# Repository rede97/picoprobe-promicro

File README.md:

# picoprobe-promicro

[中文版本](README_CN.md)

---

A Raspberry Pi Debug Probe expansion board based on the **RP2040 Pro Micro** core module. The circuit is fully compatible with the [official Raspberry Pi Debug Probe](https://www.raspberrypi.com/products/debug-probe/) — simply plug a RP2040 Pro Micro onto this board, flash the **official Debug Probe firmware from Raspberry Pi**, and you're ready to go. No custom firmware needed.

The RP2040 Pro Micro has onboard **Boot** and **Reset** buttons, making firmware flashing effortless: hold Boot → press Reset → release Boot, and a USB mass storage drive appears — just drag and drop the `.uf2` firmware file. No jumper wires or complicated steps required.

## Compatibility & Reliability

What's truly surprising is how well the Raspberry Pi Debug Probe works beyond its intended target. Its compatibility and reliability are **far beyond expectations**. It not only handles RP2040 chips perfectly, but also delivers rock-solid debugging and flashing for a wide range of **ARM microcontrollers and SoCs** — the full STM32 lineup, Nordic chips like the nRF52840, and virtually any Cortex-M core MCU.

Thanks to the RP2040's **PIO hardware**, the Debug Probe achieves exceptionally fast SWD transfer speeds, matching or exceeding some USB high-speed debuggers in practice. Over long debugging sessions across various target chips, it shows none of the common issues — no disconnections, no timeouts, no failed device recognition.

## Motivation

The official Raspberry Pi Debug Probe has a few shortcomings:

- It still uses a **Micro USB** connector, while USB-C has become the standard
- Flashing Picoprobe firmware onto a bare Pico often leads to **various stability issues**
- Designing a complete dedicated debugger PCB is overkill for many users
- It's essentially just an RP2040 + level-shifting circuit — the official price is steep for a fixed-function debug board

Meanwhile, open-source DAPLink solutions generally have **worse compatibility and stability** across ARM chips compared to the Raspberry Pi Debug Probe.

## Fully Open Source

This is one of the project's biggest strengths:

- **Fully open hardware**: All PCB design files (schematic, layout) are open source in KiCad format. Anyone can inspect, modify, or order their own boards
- **Firmware is fully open source**: Uses the official Raspberry Pi [debugprobe firmware](https://github.com/raspberrypi/debugprobe) directly — no proprietary or custom code. Maintained by Raspberry Pi, continuously updated, with guaranteed quality
- **No closed-source burden**: Many DAPLink debuggers on the market ship with proprietary firmware. When bugs appear, there's no one to report to and no way to upgrade or fix yourself. This solution is open source from hardware to firmware — community-driven and never obsolete

## Regarding JTAG

This project currently supports **SWD** only, not JTAG. From a practical standpoint:

- The vast majority of Cortex-M MCU debugging and flashing only requires SWD — JTAG is not necessary
- If you genuinely need JTAG along with Trace, ETM, and other advanced debugging features, a mature **J-Link** is the better choice — at that point you need a complete professional debugging toolchain, not just a protocol interface

Future firmware-level JTAG support is not out of the question (the RP2040's PIO is capable in hardware), but there are no concrete plans at this stage.

## Design Approach

Rather than designing a complete debugger from scratch, this project pairs a widely available **RP2040 Pro Micro** module with a dedicated expansion board:

- **Flexible**: Use pin headers and female header sockets to temporarily mount the Pro Micro on the board for debugging — detach and reuse it anytime
- **Permanent option**: Solder short pin headers to permanently join the Pro Micro and the board together as a dedicated, long-term debug probe
- **Ultra-low BOM cost**: Significantly cheaper than the official Debug Probe
- **Zero pressure**: No worries about damaging an expensive debugger — hack, modify, or build your own features on top

## PCB Renders

| Front | Back |
|:---:|:---:|
|  |  |

[Download schematic PDF](hardware/picoprobe_sch.pdf)

## Real-World Photos

This debugger works perfectly with both the **Raspberry Pi Pico 2** and the **nRF52840** — rock-solid in practice, with very fast download speeds.

### 1. Detachable socket assembly

The Pro Micro is mounted on the board via pin headers and female header sockets. Plug it in to debug; pull it off anytime and reuse the module in other projects.

### 2. Soldered as one piece

The Pro Micro is soldered directly onto the board as a single, integrated unit. This version is smaller in volume, and is otherwise **functionally identical** to the detachable version — same circuit, same performance.

### 3. Debugging an nRF52840

Debugging and flashing an nRF52840 target over SWD. Works flawlessly, with very fast download speeds.

## Project Structure

```
├── hardware/
│   ├── picoprobe.kicad_sch      # Schematic
│   ├── picoprobe.kicad_pcb      # PCB layout
│   ├── picoprobe.kicad_pro      # KiCad project file
│   ├── picoprobe-front.png      # Front render
│   ├── picoprobe-back.png       # Back render
│   ├── picoprobe_sch.pdf        # Schematic PDF
│   ├── picture/                 # Real-world photos
│   └── kicad_pro_micro_rp2040/  # Pro Micro RP2040 footprint library (submodule)
├── README.md
└── README_CN.md
```

## Dependencies

- [kicad_pro_micro_rp2040](https://github.com/rroels/kicad_pro_micro_rp2040) — KiCad symbol and footprint library for the Pro Micro RP2040

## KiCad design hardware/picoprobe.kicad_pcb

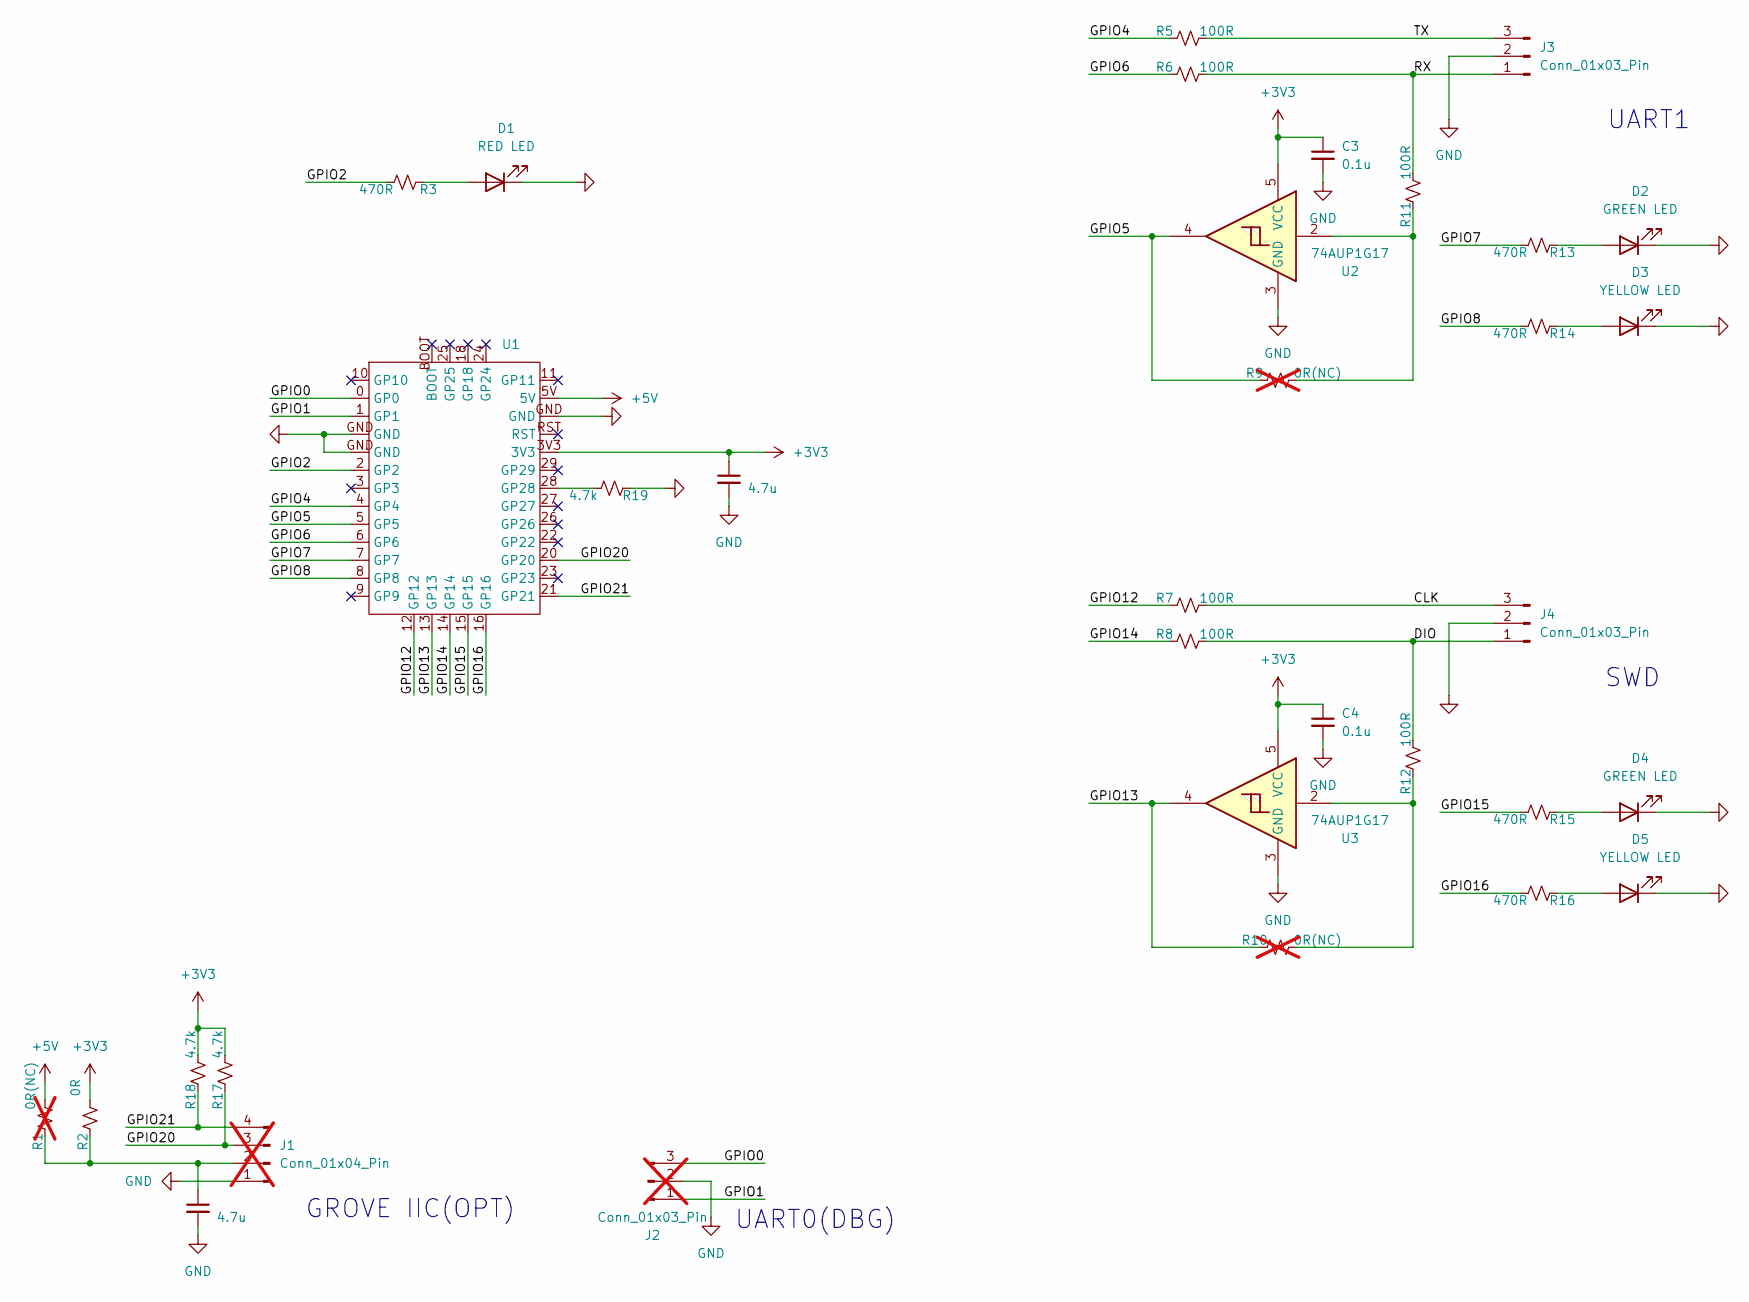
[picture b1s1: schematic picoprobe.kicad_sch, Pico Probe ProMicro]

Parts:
C1, C2: 4.7u; C_0402_1005Metric; LCSC Part C23733
C3, C4: 0.1u; C_0402_1005Metric; LCSC Part C307331
D1: RED LED; LED_0603_1608Metric; LCSC Part C2286
D2, D4: GREEN LED; LED_0603_1608Metric; LCSC Part C7496818
D3, D5: YELLOW LED; LED_0603_1608Metric; LCSC Part C965800
J1: Conn_01x04_Pin; PinHeader_1x04_P2.54mm_Vertical; not fitted
J2: Conn_01x03_Pin; PinHeader_1x03_P2.54mm_Vertical; not fitted
J3, J4: Conn_01x03_Pin; JST_XH_B3B-XH-A_1x03_P2.50mm_Vertical
R1: 0R(NC); R_0603_1608Metric; LCSC Part C21189; not fitted
R2: 0R; R_0603_1608Metric; LCSC Part C21189
R3, R13, R14, R15, R16: 470R; R_0402_1005Metric; LCSC Part C25117
R5, R6, R7, R8, R11, R12: 100R; R_0402_1005Metric; LCSC Part C25076
R9, R10: 0R(NC); R_0402_1005Metric; LCSC Part C17168; not fitted
R17, R18, R19: 4.7k; R_0402_1005Metric; LCSC Part C25900
U1: pro_micro_rp2040
U2, U3: 74AUP1G17; SOT-353_SC-70-5; LCSC Part C48946883

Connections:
+3V3: C2.1, C3.1, C4.1, R2.2, R17.2, R18.2, U1.3V3, U2.5 (VCC), U3.5 (VCC)
+5V: R1.2, U1.5V
/CLK: J4.3, R7.2
/DIO: J4.1, R8.2, R12.2
/GPIO0: J2.3, U1.0 (GP0)
/GPIO1: J2.1, U1.1 (GP1)
/GPIO2: R3.2, U1.2 (GP2)
/GPIO4: R5.1, U1.4 (GP4)
/GPIO5: R9.1, U1.5 (GP5), U2.4
/GPIO6: R6.1, U1.6 (GP6)
/GPIO7: R13.2, U1.7 (GP7)
/GPIO8: R14.2, U1.8 (GP8)
/GPIO12: R7.1, U1.12 (GP12)
/GPIO13: R10.1, U1.13 (GP13), U3.4
/GPIO14: R8.1, U1.14 (GP14)
/GPIO15: R15.2, U1.15 (GP15)
/GPIO16: R16.2, U1.16 (GP16)
/GPIO20: J1.3, R17.1, U1.20 (GP20)
/GPIO21: J1.4, R18.1, U1.21 (GP21)
/RX: J3.1, R6.2, R11.2
/TX: J3.3, R5.2
GND: C1.2, C2.2, C3.2, C4.2, D1.1 (K), D2.1 (K), D3.1 (K), D4.1 (K), D5.1 (K), J1.1, J2.2, J3.2, J4.2, R19.1, U1.GND, U2.3 (GND), U3.3 (GND)
unnamed: D1.2 (A), R3.1
unnamed: D2.2 (A), R13.1
unnamed: D3.2 (A), R14.1
unnamed: D4.2 (A), R15.1
unnamed: D5.2 (A), R16.1
unnamed: C1.1, J1.2, R1.1, R2.1
unnamed: R10.2, R12.1, U3.2
unnamed: R9.2, R11.1, U2.2
unnamed: R19.2, U1.28 (GP28)

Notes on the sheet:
UART0(DBG)
UART1
SWD
GROVE IIC(OPT)

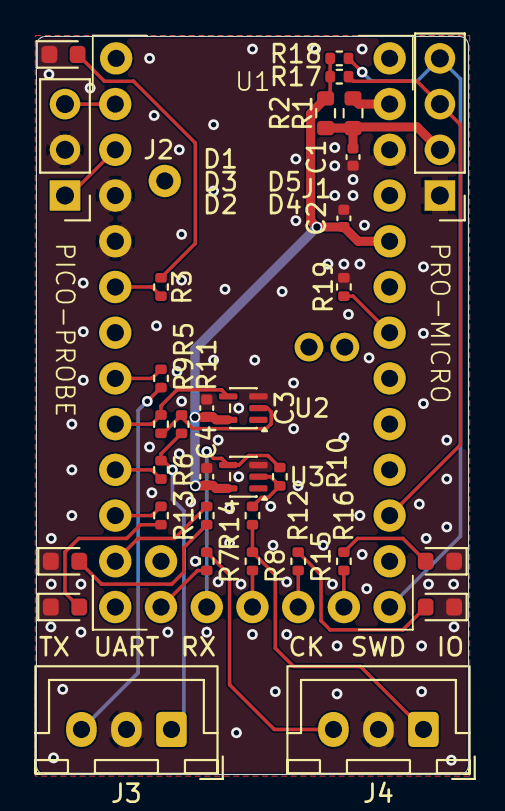
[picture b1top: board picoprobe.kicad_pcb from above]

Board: 2 copper layers, 24.0 x 41.0 mm, 34 parts (0 on the bottom side), 31 nets.

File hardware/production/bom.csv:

Designator,Footprint,Quantity,Value,LCSC Part #
"C1, C2",0402,2,4.7u,C23733
"C3, C4",0402,2,0.1u,C307331
D1,0603,1,RED LED,C2286
"D2, D4",0603,2,GREEN LED,C7496818
"D3, D5",0603,2,YELLOW LED,C965800
J1,PinHeader_1x04_P2.54mm_Vertical,1,Conn_01x04_Pin,
J2,PinHeader_1x03_P2.54mm_Vertical,1,Conn_01x03_Pin,
"J3, J4",JST_XH_B3B-XH-A_1x03_P2.50mm_Vertical,2,Conn_01x03_Pin,
"R1, R10, R9",0402,3,0R(NC),C17168
"R11, R12, R5, R6, R7, R8",0402,6,100R,C25076
"R13, R14, R15, R16, R3",0402,5,470R,C25117
"R17, R18, R19",0402,3,4.7k,C25900
R2,0402,1,0R,C17168
U1,pro_micro_rp2040,1,~,
"U2, U3",SOT-23-5,2,74AUP1G17,C48946883

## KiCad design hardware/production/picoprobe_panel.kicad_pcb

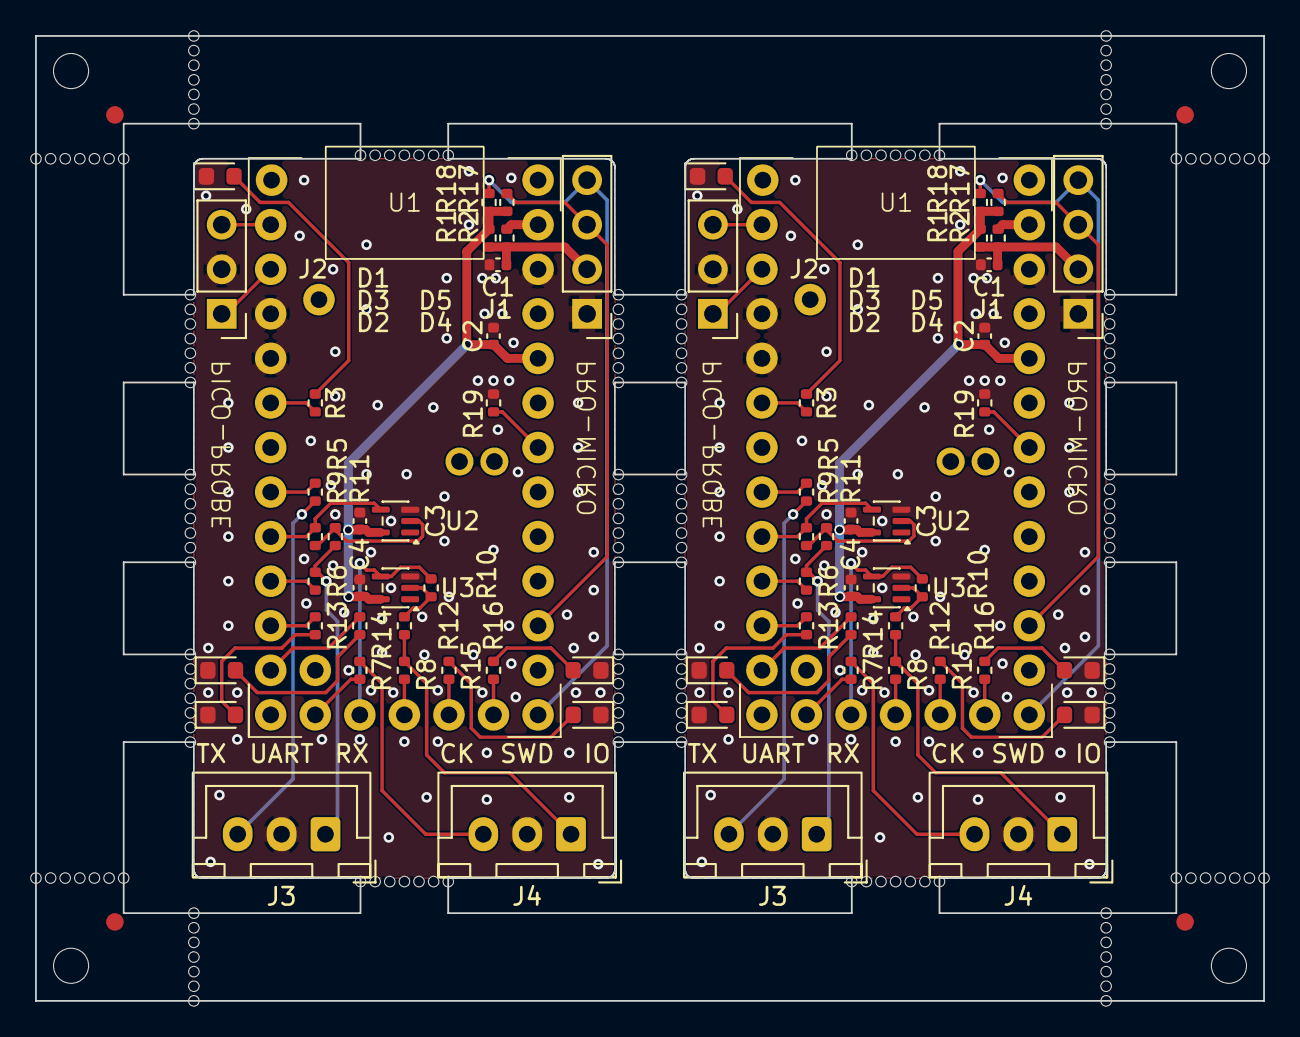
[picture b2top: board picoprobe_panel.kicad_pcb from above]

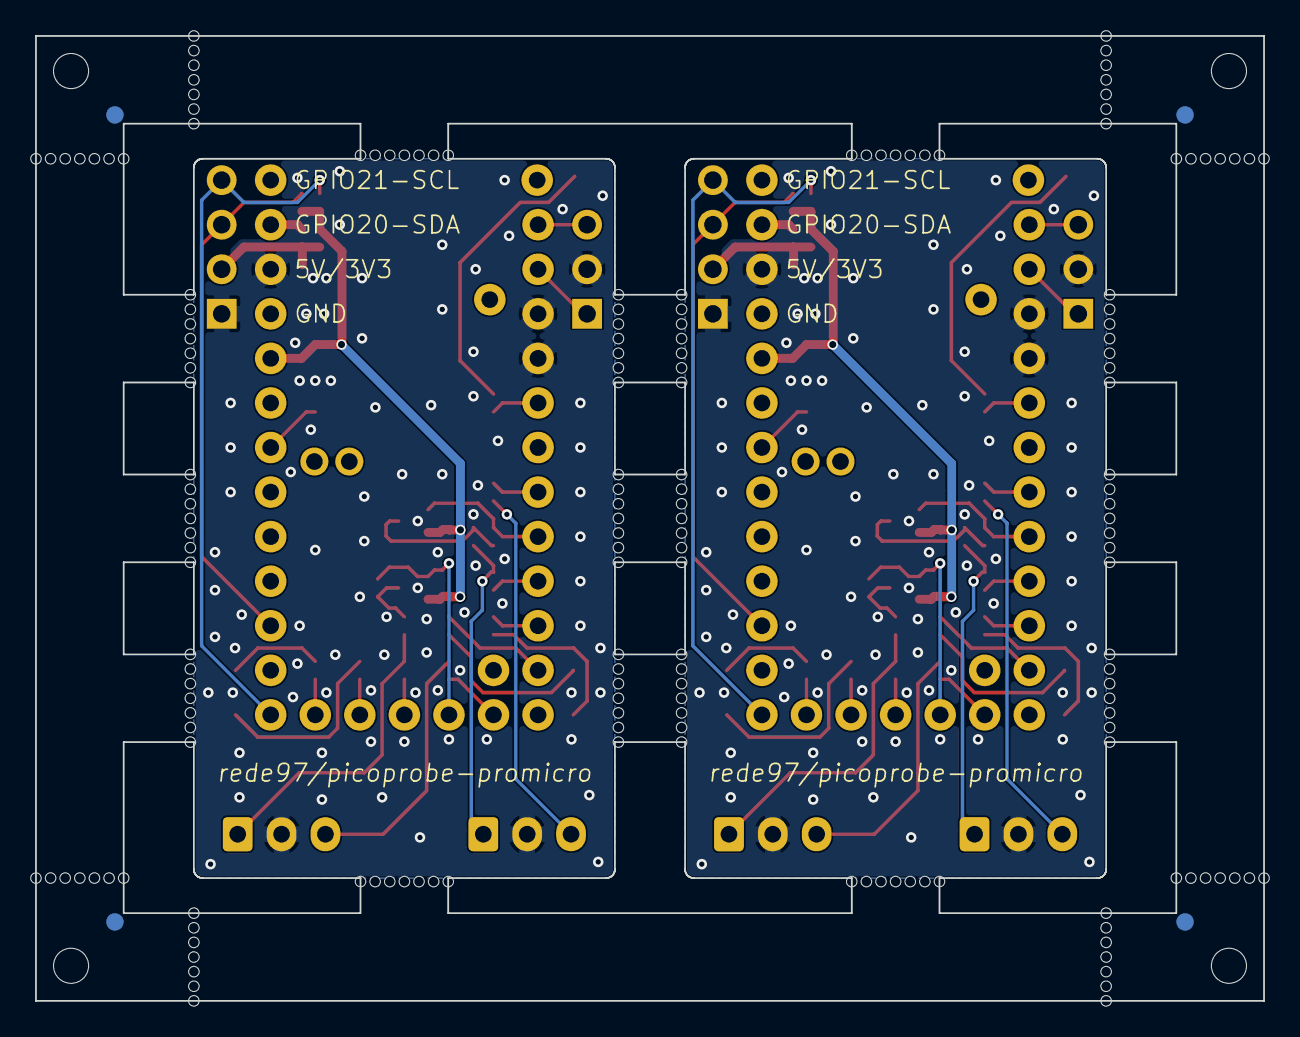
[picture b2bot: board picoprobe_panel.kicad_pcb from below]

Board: 2 copper layers, 70.0 x 55.0 mm, 248 parts (4 on the bottom side), 62 nets.

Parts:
C1, C1#2, C2, C2#2: 4.7u; C_0402_1005Metric
C3, C3#2, C4, C4#2: 0.1u; C_0402_1005Metric
D1, D1#2: RED LED; LED_0603_1608Metric
D2, D2#2, D4, D4#2: GREEN LED; LED_0603_1608Metric
D3, D3#2, D5, D5#2: YELLOW LED; LED_0603_1608Metric
J1, J1#2: Conn_01x04_Pin; PinHeader_1x04_P2.54mm_Vertical
J2, J2#2: Conn_01x03_Pin; PinHeader_1x03_P2.54mm_Vertical
J3, J3#2, J4, J4#2: Conn_01x03_Pin; JST_XH_B3B-XH-A_1x03_P2.50mm_Vertical
KiKit_FID_B_1, KiKit_FID_B_2, KiKit_FID_B_3, KiKit_FID_B_4: Fiducial
KiKit_FID_T_1, KiKit_FID_T_2, KiKit_FID_T_3, KiKit_FID_T_4: Fiducial
KiKit_MB_1_1, KiKit_MB_1_2, KiKit_MB_1_3, KiKit_MB_1_4, KiKit_MB_1_5, KiKit_MB_1_6, KiKit_MB_1_7, KiKit_MB_2_1, KiKit_MB_2_2, KiKit_MB_2_3, KiKit_MB_2_4, KiKit_MB_2_5, KiKit_MB_2_6, KiKit_MB_2_7, KiKit_MB_3_1, KiKit_MB_3_2, KiKit_MB_3_3, KiKit_MB_3_4, KiKit_MB_3_5, KiKit_MB_3_6, KiKit_MB_3_7, KiKit_MB_4_1, KiKit_MB_4_2, KiKit_MB_4_3, KiKit_MB_4_4, KiKit_MB_4_5, KiKit_MB_4_6, KiKit_MB_4_7, KiKit_MB_5_1, KiKit_MB_5_2, KiKit_MB_5_3, KiKit_MB_5_4, KiKit_MB_5_5, KiKit_MB_5_6, KiKit_MB_5_7, KiKit_MB_6_1, KiKit_MB_6_2, KiKit_MB_6_3, KiKit_MB_6_4, KiKit_MB_6_5, KiKit_MB_6_6, KiKit_MB_6_7, KiKit_MB_7_1, KiKit_MB_7_2, KiKit_MB_7_3, KiKit_MB_7_4, KiKit_MB_7_5, KiKit_MB_7_6, KiKit_MB_7_7, KiKit_MB_8_1, KiKit_MB_8_2, KiKit_MB_8_3, KiKit_MB_8_4, KiKit_MB_8_5, KiKit_MB_8_6, KiKit_MB_8_7, KiKit_MB_9_1, KiKit_MB_9_2, KiKit_MB_9_3, KiKit_MB_9_4, KiKit_MB_9_5, KiKit_MB_9_6, KiKit_MB_9_7, KiKit_MB_10_1, KiKit_MB_10_2, KiKit_MB_10_3, KiKit_MB_10_4, KiKit_MB_10_5, KiKit_MB_10_6, KiKit_MB_10_7, KiKit_MB_11_1, KiKit_MB_11_2, KiKit_MB_11_3, KiKit_MB_11_4, KiKit_MB_11_5, KiKit_MB_11_6, KiKit_MB_11_7, KiKit_MB_12_1, KiKit_MB_12_2, KiKit_MB_12_3, KiKit_MB_12_4, KiKit_MB_12_5, KiKit_MB_12_6, KiKit_MB_12_7, KiKit_MB_13_1, KiKit_MB_13_2, KiKit_MB_13_3, KiKit_MB_13_4, KiKit_MB_13_5, KiKit_MB_13_6, KiKit_MB_13_7, KiKit_MB_14_1, KiKit_MB_14_2, KiKit_MB_14_3, KiKit_MB_14_4, KiKit_MB_14_5, KiKit_MB_14_6, KiKit_MB_14_7, KiKit_MB_15_1, KiKit_MB_15_2, KiKit_MB_15_3, KiKit_MB_15_4, KiKit_MB_15_5, KiKit_MB_15_6, KiKit_MB_15_7, KiKit_MB_16_1, KiKit_MB_16_2, KiKit_MB_16_3, KiKit_MB_16_4, KiKit_MB_16_5, KiKit_MB_16_6, KiKit_MB_16_7, KiKit_MB_17_1, KiKit_MB_17_2, KiKit_MB_17_3, KiKit_MB_17_4, KiKit_MB_17_5, KiKit_MB_17_6, KiKit_MB_17_7, KiKit_MB_18_1, KiKit_MB_18_2, KiKit_MB_18_3, KiKit_MB_18_4, KiKit_MB_18_5, KiKit_MB_18_6, KiKit_MB_18_7, KiKit_MB_19_1, KiKit_MB_19_2, KiKit_MB_19_3, KiKit_MB_19_4, KiKit_MB_19_5, KiKit_MB_19_6, KiKit_MB_19_7, KiKit_MB_20_1, KiKit_MB_20_2, KiKit_MB_20_3, KiKit_MB_20_4, KiKit_MB_20_5, KiKit_MB_20_6, KiKit_MB_20_7, KiKit_MB_21_1, KiKit_MB_21_2, KiKit_MB_21_3, KiKit_MB_21_4, KiKit_MB_21_5, KiKit_MB_21_6, KiKit_MB_21_7, KiKit_MB_22_1, KiKit_MB_22_2, KiKit_MB_22_3, KiKit_MB_22_4, KiKit_MB_22_5, KiKit_MB_22_6, KiKit_MB_22_7, KiKit_MB_23_1, KiKit_MB_23_2, KiKit_MB_23_3, KiKit_MB_23_4, KiKit_MB_23_5, KiKit_MB_23_6, KiKit_MB_23_7, KiKit_MB_24_1, KiKit_MB_24_2, KiKit_MB_24_3, KiKit_MB_24_4, KiKit_MB_24_5, KiKit_MB_24_6, KiKit_MB_24_7: NPTH
KiKit_TO_1, KiKit_TO_2, KiKit_TO_3, KiKit_TO_4: NPTH
R1, R1#2, R9, R9#2, R10, R10#2: 0R(NC); R_0402_1005Metric
R2, R2#2: 0R; R_0402_1005Metric
R3, R3#2, R13, R13#2, R14, R14#2, R15, R15#2, R16, R16#2: 470R; R_0402_1005Metric
R5, R5#2, R6, R6#2, R7, R7#2, R8, R8#2, R11, R11#2, R12, R12#2: 100R; R_0402_1005Metric
R17, R17#2, R18, R18#2, R19, R19#2: 4.7k; R_0402_1005Metric
U1, U1#2: pro_micro_rp2040
U2, U2#2, U3, U3#2: 74AUP1G17; SOT-353_SC-70-5

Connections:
Board_0-+3V3: C2#2.1, C3.1, C4.1, R2#2.2, R17#2.2, R18.2, U1#2.3V3, U2#2.5 (VCC), U3#2.5 (VCC)
Board_0-+5V: R1.2, U1#2.5V
Board_0-/CLK: J4.3, R7#2.2
Board_0-/DIO: J4.1, R8.2, R12.2
Board_0-/GPIO0: J2.3, U1#2.0 (GP0)
Board_0-/GPIO1: J2.1, U1#2.1 (GP1)
Board_0-/GPIO2: R3#2.2, U1#2.2 (GP2)
Board_0-/GPIO4: R5.1, U1#2.4 (GP4)
Board_0-/GPIO5: R9.1, U1#2.5 (GP5), U2#2.4
Board_0-/GPIO6: R6.1, U1#2.6 (GP6)
Board_0-/GPIO7: R13.2, U1#2.7 (GP7)
Board_0-/GPIO8: R14.2, U1#2.8 (GP8)
Board_0-/GPIO12: R7#2.1, U1#2.12 (GP12)
Board_0-/GPIO13: R10#2.1, U1#2.13 (GP13), U3#2.4
Board_0-/GPIO14: R8.1, U1#2.14 (GP14)
Board_0-/GPIO15: R15.2, U1#2.15 (GP15)
Board_0-/GPIO16: R16.2, U1#2.16 (GP16)
Board_0-/GPIO20: J1.3, R17#2.1, U1#2.20 (GP20)
Board_0-/GPIO21: J1.4, R18.1, U1#2.21 (GP21)
Board_0-/RX: J3#2.1, R6.2, R11#2.2
Board_0-/TX: J3#2.3, R5.2
Board_0-GND: C1.2, C2#2.2, C3.2, C4.2, D1#2.1 (K), D2.1 (K), D3.1 (K), D4.1 (K), D5.1 (K), J1.1, J2.2, J3#2.2, J4.2, R19#2.1, U1#2.GND, U2#2.3 (GND), U3#2.3 (GND)
Board_0-Net-(D1-A): D1#2.2 (A), R3#2.1
Board_0-Net-(D2-A): D2.2 (A), R13.1
Board_0-Net-(D3-A): D3.2 (A), R14.1
Board_0-Net-(D4-A): D4.2 (A), R15.1
Board_0-Net-(D5-A): D5.2 (A), R16.1
Board_0-Net-(J1-Pin_2): C1.1, J1.2, R1.1, R2#2.1
Board_0-Net-(R10-Pad2): R10#2.2, R12.1, U3#2.2
Board_0-Net-(R11-Pad1): R9.2, R11#2.1, U2#2.2
Board_0-Net-(U1-GP28): R19#2.2, U1#2.28 (GP28)
Board_1-+3V3: C2.1, C3#2.1, C4#2.1, R2.2, R17.2, R18#2.2, U1.3V3, U2.5 (VCC), U3.5 (VCC)
Board_1-+5V: R1#2.2, U1.5V
Board_1-/CLK: J4#2.3, R7.2
Board_1-/DIO: J4#2.1, R8#2.2, R12#2.2
Board_1-/GPIO0: J2#2.3, U1.0 (GP0)
Board_1-/GPIO1: J2#2.1, U1.1 (GP1)
Board_1-/GPIO2: R3.2, U1.2 (GP2)
Board_1-/GPIO4: R5#2.1, U1.4 (GP4)
Board_1-/GPIO5: R9#2.1, U1.5 (GP5), U2.4
Board_1-/GPIO6: R6#2.1, U1.6 (GP6)
Board_1-/GPIO7: R13#2.2, U1.7 (GP7)
Board_1-/GPIO8: R14#2.2, U1.8 (GP8)
Board_1-/GPIO12: R7.1, U1.12 (GP12)
Board_1-/GPIO13: R10.1, U1.13 (GP13), U3.4
Board_1-/GPIO14: R8#2.1, U1.14 (GP14)
Board_1-/GPIO15: R15#2.2, U1.15 (GP15)
Board_1-/GPIO16: R16#2.2, U1.16 (GP16)
Board_1-/GPIO20: J1#2.3, R17.1, U1.20 (GP20)
Board_1-/GPIO21: J1#2.4, R18#2.1, U1.21 (GP21)
Board_1-/RX: J3.1, R6#2.2, R11.2
Board_1-/TX: J3.3, R5#2.2
Board_1-GND: C1#2.2, C2.2, C3#2.2, C4#2.2, D1.1 (K), D2#2.1 (K), D3#2.1 (K), D4#2.1 (K), D5#2.1 (K), J1#2.1, J2#2.2, J3.2, J4#2.2, R19.1, U1.GND, U2.3 (GND), U3.3 (GND)
Board_1-Net-(D1-A): D1.2 (A), R3.1
Board_1-Net-(D2-A): D2#2.2 (A), R13#2.1
Board_1-Net-(D3-A): D3#2.2 (A), R14#2.1
Board_1-Net-(D4-A): D4#2.2 (A), R15#2.1
Board_1-Net-(D5-A): D5#2.2 (A), R16#2.1
Board_1-Net-(J1-Pin_2): C1#2.1, J1#2.2, R1#2.1, R2.1
Board_1-Net-(R10-Pad2): R10.2, R12#2.1, U3.2
Board_1-Net-(R11-Pad1): R9#2.2, R11.1, U2.2
Board_1-Net-(U1-GP28): R19.2, U1.28 (GP28)
